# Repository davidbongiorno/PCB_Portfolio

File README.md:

# PCB_Portfolio
This is a repository of previous schematics and layouts used in some of my prior work and personal projects!

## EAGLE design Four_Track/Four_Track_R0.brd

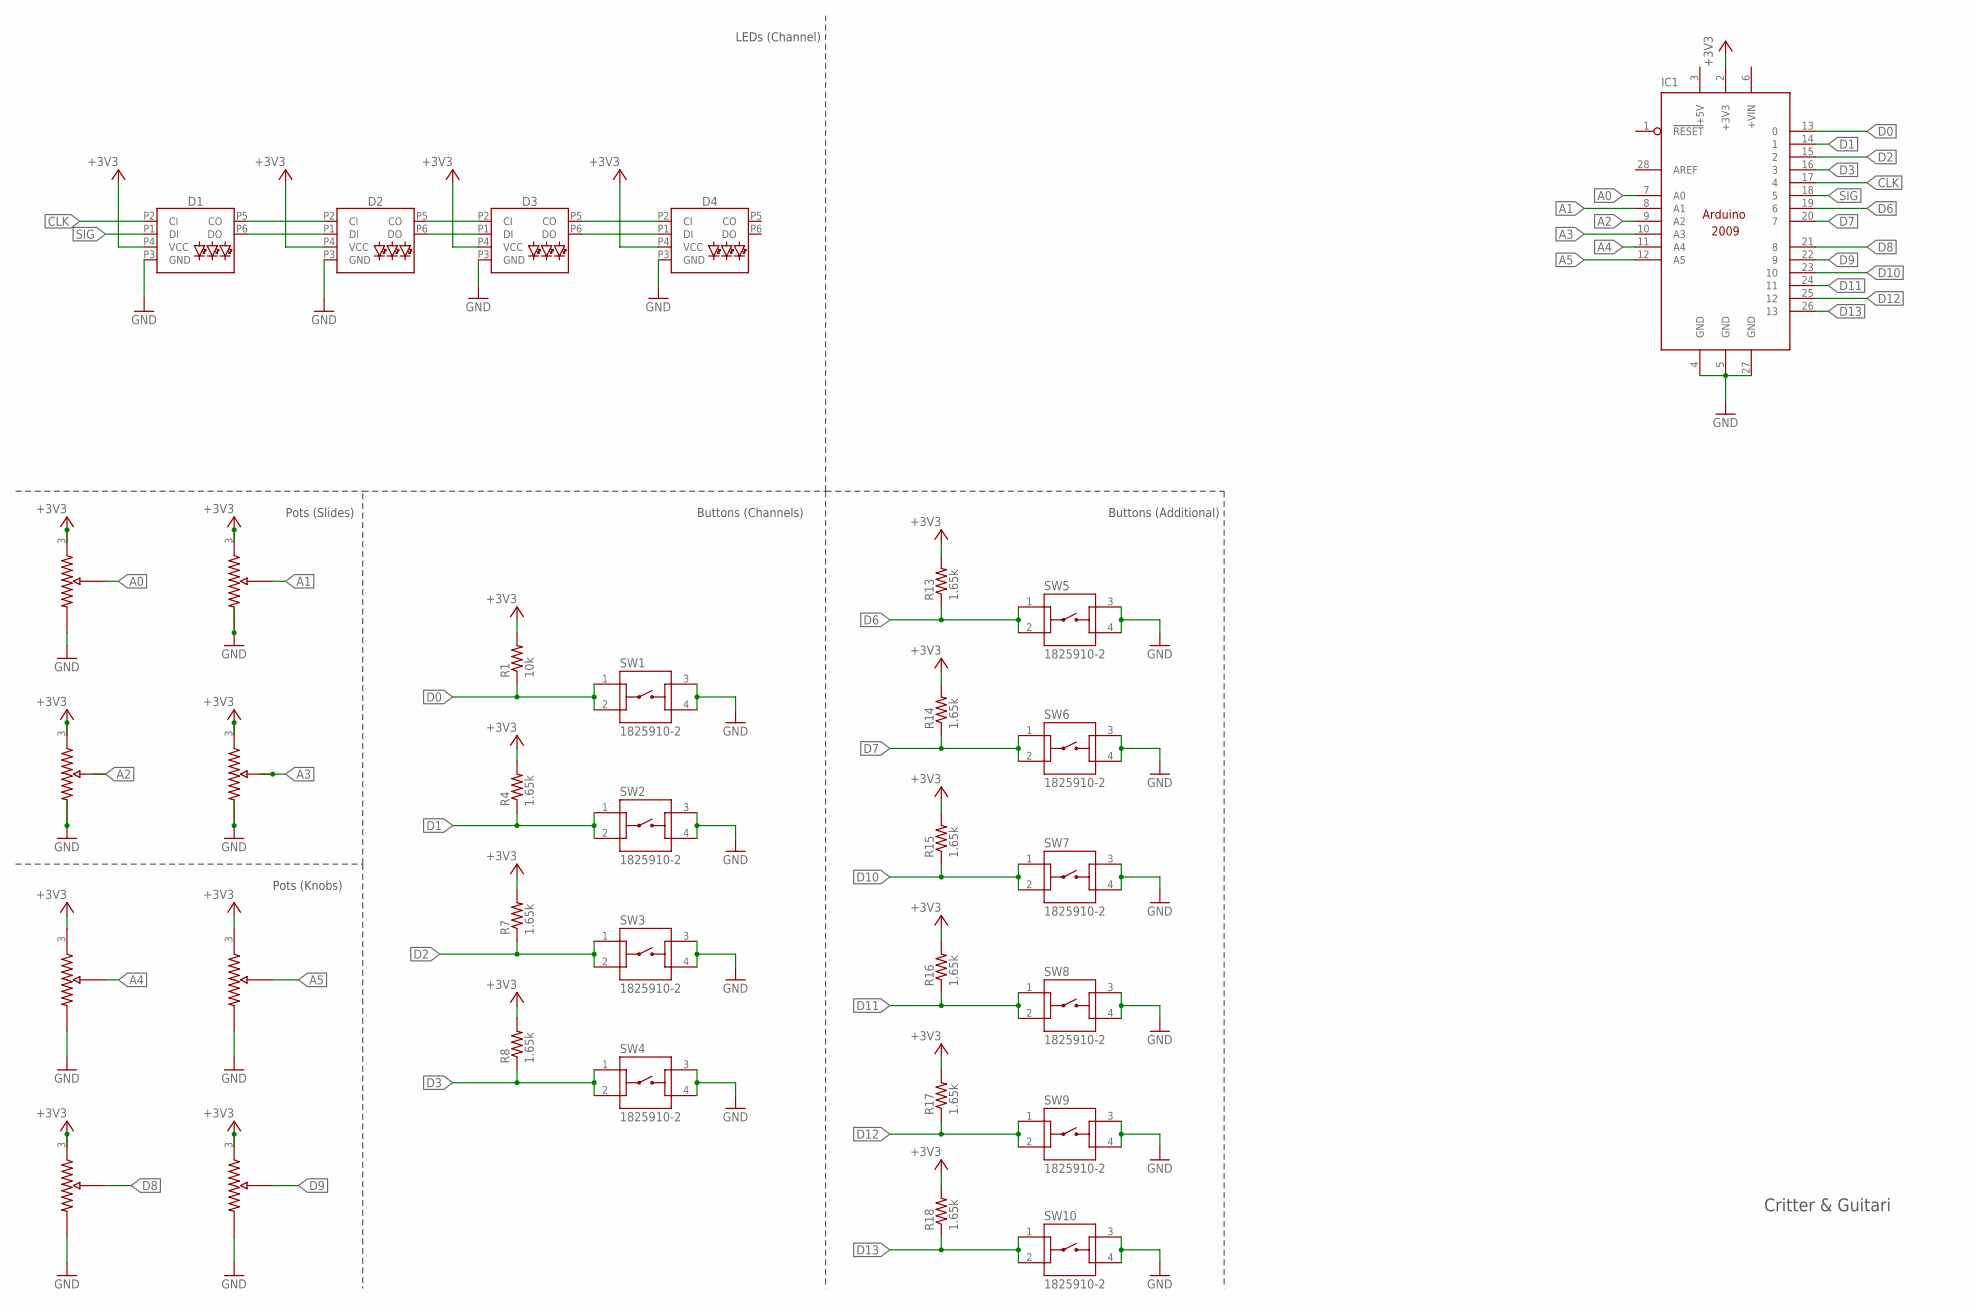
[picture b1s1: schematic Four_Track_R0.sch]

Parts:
D1, D2, D3, D4: SPARKFUN-LED_APA102-5050
IC1: ARDUINO2009_10; ARDUINO2009
R1: 10k; R0603
R2, R3, R5, R11: POTPTA45; SLIDE_POT_PTA4543
R4, R7, R8, R13, R14, R15, R16, R17, R18: 1.65k; R0603
R6, R9, R10, R12: POTVERT; POT-P09X-VERT
SW1, SW2, SW3, SW4, SW5, SW6, SW7, SW8, SW9, SW10: 1825910-2; TE_1825910-2

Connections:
+3V3: D1.P4 (VCC), D2.P4 (VCC), D3.P4 (VCC), D4.P4 (VCC), IC1.2 (+3V3), R1.2, R2.3, R3.3, R4.2, R5.3, R6.3, R7.2, R8.2, R9.3, R10.3, R11.3, R12.3, R13.2, R14.2, R15.2, R16.2, R17.2, R18.2
+5V: IC1.3 (+5V)
A0: IC1.7 (A0), R11.2
A1: IC1.8 (A1), R5.2
A2: IC1.9 (A2), R2.2
A3: IC1.10 (A3), R3.2
A4: IC1.11 (A4), R9.WIPER
A5: IC1.12 (A5), R10.WIPER
CLK: D1.P2 (CI), IC1.17 (4)
D0: IC1.13 (0), R1.1, SW1.1, SW1.2
D1: IC1.14 (1), R4.1, SW2.1, SW2.2
D2: IC1.15 (2), R7.1, SW3.1, SW3.2
D3: IC1.16 (3), R8.1, SW4.1, SW4.2
D6: IC1.19 (6), R13.1, SW5.1, SW5.2
D7: IC1.20 (7), R14.1, SW6.1, SW6.2
D8: IC1.21 (8), R6.WIPER
D9: IC1.22 (9), R12.WIPER
D10: IC1.23 (10), R15.1, SW7.1, SW7.2
D11: IC1.24 (11), R16.1, SW8.1, SW8.2
D12: IC1.25 (12), R17.1, SW9.1, SW9.2
D13: IC1.26 (13), R18.1, SW10.1, SW10.2
GND: D1.P3 (GND), D2.P3 (GND), D3.P3 (GND), D4.P3 (GND), IC1.4 (GND), IC1.5 (GND), IC1.27 (GND), R2.1, R3.1, R5.1, R6.1, R9.1, R10.1, R11.1, R12.1, SW1.3, SW1.4, SW2.3, SW2.4, SW3.3, SW3.4, SW4.3, SW4.4, SW5.3, SW5.4, SW6.3, SW6.4, SW7.3, SW7.4, SW8.3, SW8.4, SW9.3, SW9.4, SW10.3, SW10.4
unnamed: D1.P5 (CO), D2.P2 (CI)
unnamed: D1.P6 (DO), D2.P1 (DI)
unnamed: D2.P6 (DO), D3.P1 (DI)
unnamed: D2.P5 (CO), D3.P2 (CI)
unnamed: D3.P6 (DO), D4.P1 (DI)
unnamed: D3.P5 (CO), D4.P2 (CI)
SIG: D1.P1 (DI), IC1.18 (5)

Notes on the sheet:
Critter & Guitari
Buttons (Channels)
Pots (Knobs)
Pots (Slides)
Buttons (Additional)
LEDs (Channel)

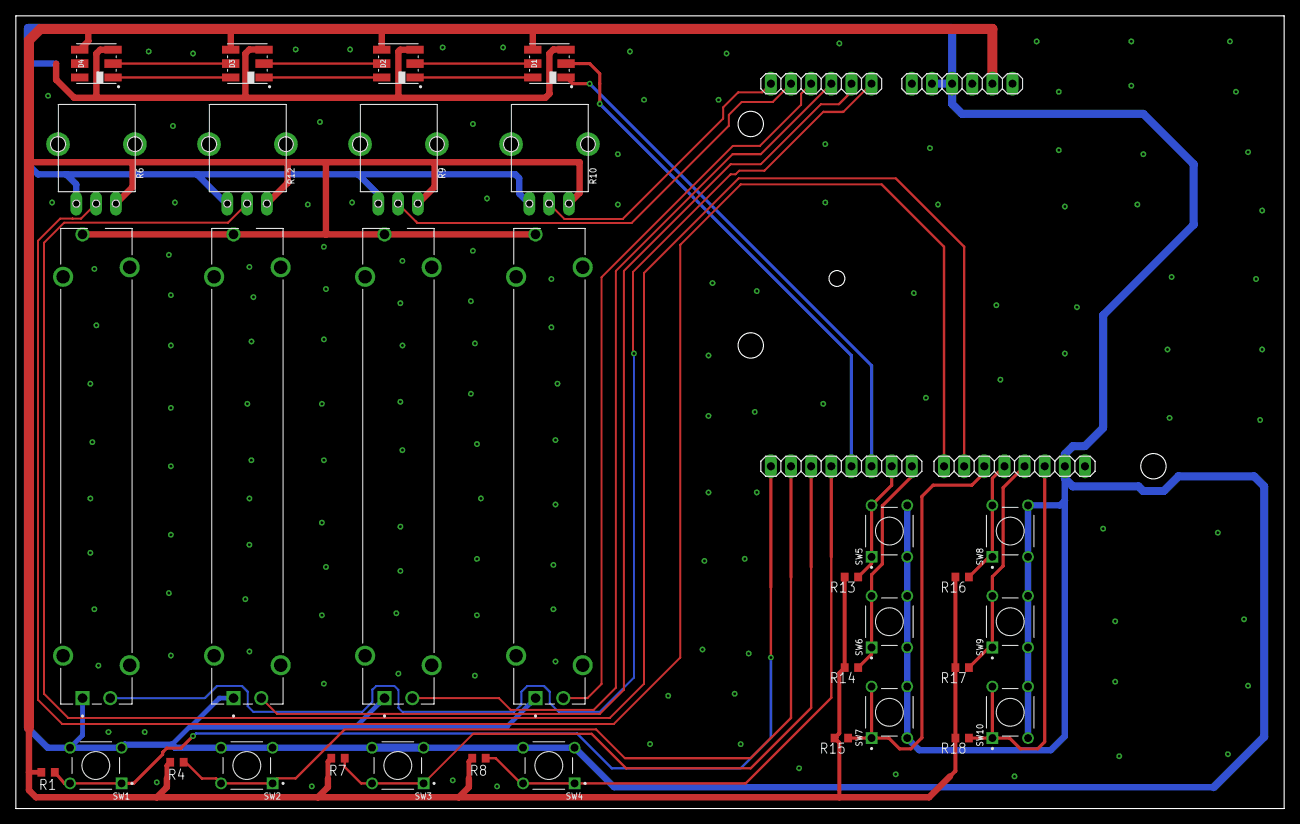
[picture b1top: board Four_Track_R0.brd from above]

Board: 2 copper layers, 160.0 x 100.0 mm, 33 parts (0 on the bottom side), 28 nets.

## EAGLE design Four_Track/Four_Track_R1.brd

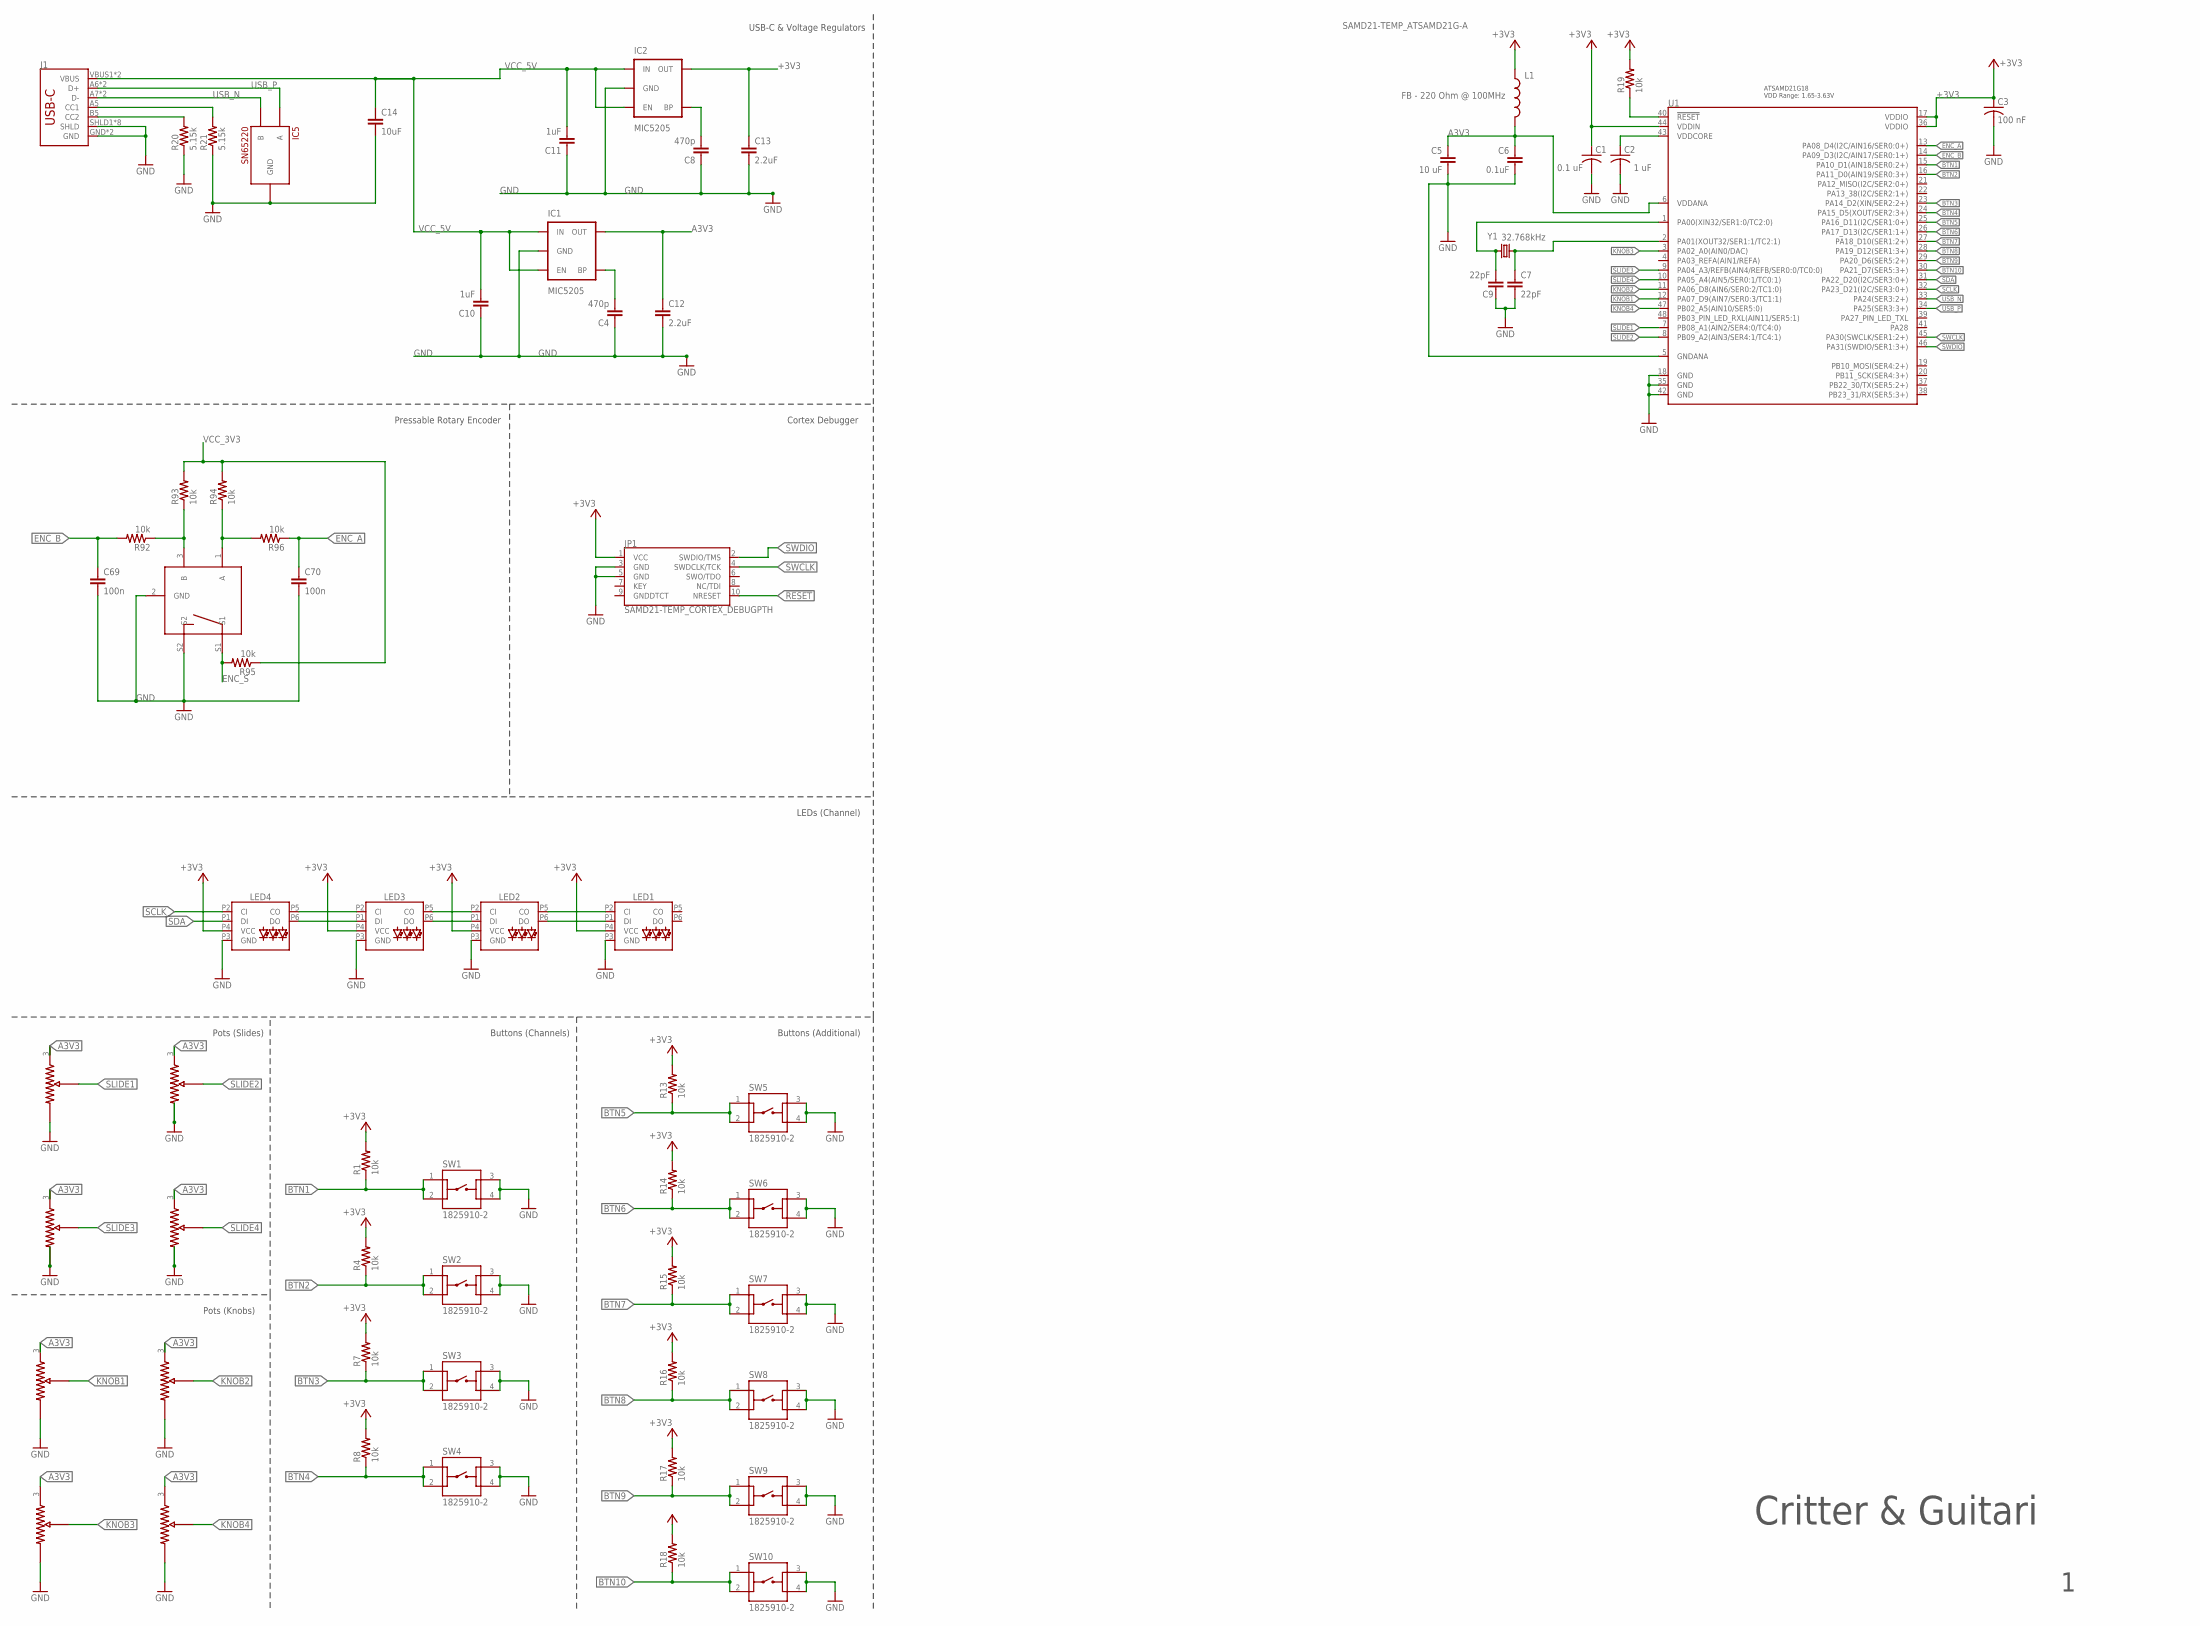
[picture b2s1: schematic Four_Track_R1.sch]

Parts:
C1: 0.1 uF; C0603
C2: 1 uF; C0603
C3: 100 nF; C0603
C4, C8: 470p; 0603-CAP
C5: 10 uF; 0603-CAP
C6: 0.1uF; 0603-CAP
C7, C9: 22pF; 0603-CAP
C10, C11: 1uF; 0603-CAP
C12, C13: 2.2uF; C0805
C14: 10uF; C1206
C69, C70: 100n; 0603-CAP
IC1, IC2: MIC5205; SPARKFUN-3-2-07_SOT23-5
IC5: SN65220; SOT23-6L
J1: SPARKFUN-CONNECTORS_USB_C16PIN; SPARKFUN-CONNECTORS_USB-C-16P
JP1: SAMD21-TEMP_CORTEX_DEBUGPTH; SAMD21-TEMP_2X5-PTH-1.27MM
L1: FB - 220 Ohm @ 100MHz; 0603
LED1, LED2, LED3, LED4: SPARKFUN-LED_APA102-5050
R1, R4, R7, R8, R13, R14, R15, R16, R17, R18, R19: 10k; R0603
R2, R3, R5, R11: POTPTA45; SLIDE_POT_PTA4543
R6, R9, R10, R12: POTVERT; POT-P09X-VERT
R20, R21: 5.15k; R0603
R92, R93, R94, R95, R96: 10k; 0603-RES
S3: ENCODER_SWITCH
SW1, SW2, SW3, SW4, SW5, SW6, SW7, SW8, SW9, SW10: 1825910-2; TE_1825910-2
U1: SAMD21-TEMP_ATSAMD21G-A; SAMD21-TEMP_TQFP-48
Y1: 32.768kHz; CRYSTAL-SMD-3.2X1.5MM

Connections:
!RESET: JP1.10 (NRESET), R19.1, U1.40 (!RESET!)
+3V3: C1.1, C3.1, C13.1, IC2.5 (OUT), JP1.1 (VCC), L1.1, LED1.P4 (VCC), LED2.P4 (VCC), LED3.P4 (VCC), LED4.P4 (VCC), R1.2, R4.2, R7.2, R8.2, R13.2, R14.2, R15.2, R16.2, R17.2, R18.2, R19.2, U1.17 (VDDIO), U1.36 (VDDIO), U1.44 (VDDIN)
A3V3: C5.1, C6.1, C12.1, IC1.5 (OUT), L1.2, R2.3, R3.3, R5.3, R6.3, R9.3, R10.3, R11.3, R12.3, U1.6 (VDDANA)
BTN1: R1.1, SW1.1, SW1.2, U1.15 (PA10_D1(AIN18/SER0:2+))
BTN2: R4.1, SW2.1, SW2.2, U1.16 (PA11_D0(AIN19/SER0:3+))
BTN3: R7.1, SW3.1, SW3.2, U1.23 (PA14_D2(XIN/SER2:2+))
BTN4: R8.1, SW4.1, SW4.2, U1.24 (PA15_D5(XOUT/SER2:3+))
BTN5: R13.1, SW5.1, SW5.2, U1.25 (PA16_D11(I2C/SER1:0+))
BTN6: R14.1, SW6.1, SW6.2, U1.26 (PA17_D13(I2C/SER1:1+))
BTN7: R15.1, SW7.1, SW7.2, U1.27 (PA18_D10(SER1:2+))
BTN8: R16.1, SW8.1, SW8.2, U1.28 (PA19_D12(SER1:3+))
BTN9: R17.1, SW9.1, SW9.2, U1.29 (PA20_D6(SER5:2+))
BTN10: R18.1, SW10.1, SW10.2, U1.30 (PA21_D7(SER5:3+))
ENC_A: C70.1, R96.1, U1.13 (PA08_D4(I2C/AIN16/SER0:0+))
ENC_B: C69.1, R92.2, U1.14 (PA09_D3(I2C/AIN17/SER0:1+))
ENC_S: R95.2, S3.S1
GND: C1.2, C2.2, C3.2, C4.1, C5.2, C6.2, C7.2, C8.1, C9.1, C10.1, C11.1, C12.2, C13.2, C14.2, C69.2, C70.2, IC1.2 (GND), IC2.2 (GND), IC5.2 (GND), IC5.5 (GND), J1.GND, J1.GND2 (GND), J1.SHLD1 (SHLD), J1.SHLD2 (SHLD), J1.SHLD3 (SHLD), J1.SHLD4 (SHLD), J1.SHLD5 (SHLD), J1.SHLD6 (SHLD), J1.SHLD7 (SHLD), J1.SHLD8 (SHLD), JP1.3 (GND), JP1.5 (GND), LED1.P3 (GND), LED2.P3 (GND), LED3.P3 (GND), LED4.P3 (GND), R2.1, R3.1, R5.1, R6.1, R9.1, R10.1, R11.1, R12.1, R20.1, R21.1, S3.2 (GND), S3.S2, SW1.3, SW1.4, SW2.3, SW2.4, SW3.3, SW3.4, SW4.3, SW4.4, SW5.3, SW5.4, SW6.3, SW6.4, SW7.3, SW7.4, SW8.3, SW8.4, SW9.3, SW9.4, SW10.3, SW10.4, U1.5 (GNDANA), U1.18 (GND), U1.35 (GND), U1.42 (GND)
KNOB1: R6.WIPER, U1.12 (PA07_D9(AIN7/SER0:3/TC1:1))
KNOB2: R12.WIPER, U1.11 (PA06_D8(AIN6/SER0:2/TC1:0))
KNOB3: R9.WIPER, U1.3 (PA02_A0(AIN0/DAC))
KNOB4: R10.WIPER, U1.47 (PB02_A5(AIN10/SER5:0))
unnamed: J1.B5 (CC2), R20.2
unnamed: LED3.P2 (CI), LED4.P5 (CO)
unnamed: LED3.P1 (DI), LED4.P6 (DO)
unnamed: LED2.P1 (DI), LED3.P6 (DO)
unnamed: LED2.P2 (CI), LED3.P5 (CO)
unnamed: LED1.P1 (DI), LED2.P6 (DO)
unnamed: LED1.P2 (CI), LED2.P5 (CO)
unnamed: J1.A5 (CC1), R21.2
unnamed: C4.2, IC1.4 (BP)
unnamed: C8.2, IC2.4 (BP)
unnamed: C7.1, U1.2 (PA01(XOUT32/SER1:1/TC2:1)), Y1.P$1 (1)
unnamed: C9.2, U1.1 (PA00(XIN32/SER1:0/TC2:0)), Y1.P$2 (2)
unnamed: R92.1, R93.1, S3.3 (B)
unnamed: R94.1, R96.2, S3.1 (A)
SCLK: LED4.P2 (CI), U1.32 (PA23_D21(I2C/SER3:0+))
SDA: LED4.P1 (DI), U1.31 (PA22_D20(I2C/SER3:0+))
SLIDE1: R11.2, U1.7 (PB08_A1(AIN2/SER4:0/TC4:0))
SLIDE2: R5.2, U1.8 (PB09_A2(AIN3/SER4:1/TC4:1))
SLIDE3: R2.2, U1.9 (PA04_A3/REFB(AIN4/REFB/SER0:0/TC0:0))
SLIDE4: R3.2, U1.10 (PA05_A4(AIN5/SER0:1/TC0:1))
SWCLK: JP1.4 (SWDCLK/TCK), U1.45 (PA30(SWCLK/SER1:2+))
SWDIO: JP1.2 (SWDIO/TMS), U1.46 (PA31(SWDIO/SER1:3+))
USB_N: IC5.4 (B), J1.A7 (D-), J1.B7 (D-), U1.33 (PA24(SER3:2+))
USB_P: IC5.6 (A), J1.A6 (D+), J1.B6 (D+), U1.34 (PA25(SER3:3+))
VCC_3V3: R93.2, R94.2, R95.1
VCC_5V: C10.2, C11.2, C14.1, IC1.1 (IN), IC1.3 (EN), IC2.1 (IN), IC2.3 (EN), J1.VBUS1 (VBUS), J1.VBUS2 (VBUS)
VDDCORE: C2.1, U1.43 (VDDCORE)

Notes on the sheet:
Critter & Guitari
Buttons (Channels)
Pots (Knobs)
Pots (Slides)
Buttons (Additional)
LEDs (Channel)
ATSAMD21G18 VDD Range: 1.65-3.63V
USB-C & Voltage Regulators
Cortex Debugger
Pressable Rotary Encoder

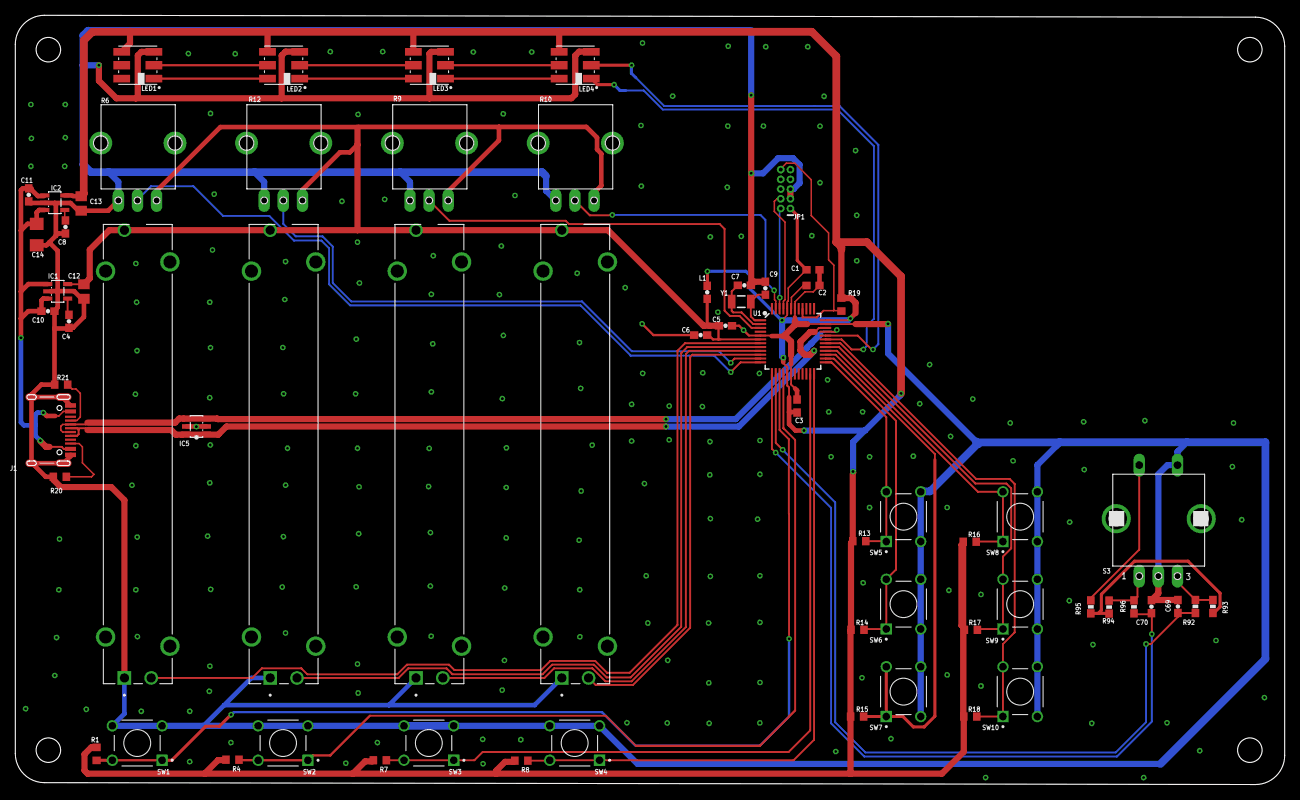
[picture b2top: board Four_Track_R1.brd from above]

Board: 2 copper layers, 165.8 x 100.5 mm, 69 parts (0 on the bottom side), 48 nets.

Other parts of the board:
H$1: INSULATED_HOLE
U$1, U$2, U$3: INSULATED_HOLE

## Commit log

2021-09-06 Added Four Track schematics & layouts from work @ C&G
2021-09-06 Obligatory .DS_Store removal

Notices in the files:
parts and their libraries:
SparkFun-Capacitors: Licensing: Creative Commons ShareAlike 4.0 International - https://creativecommons.org/licenses/by-sa/4.0
